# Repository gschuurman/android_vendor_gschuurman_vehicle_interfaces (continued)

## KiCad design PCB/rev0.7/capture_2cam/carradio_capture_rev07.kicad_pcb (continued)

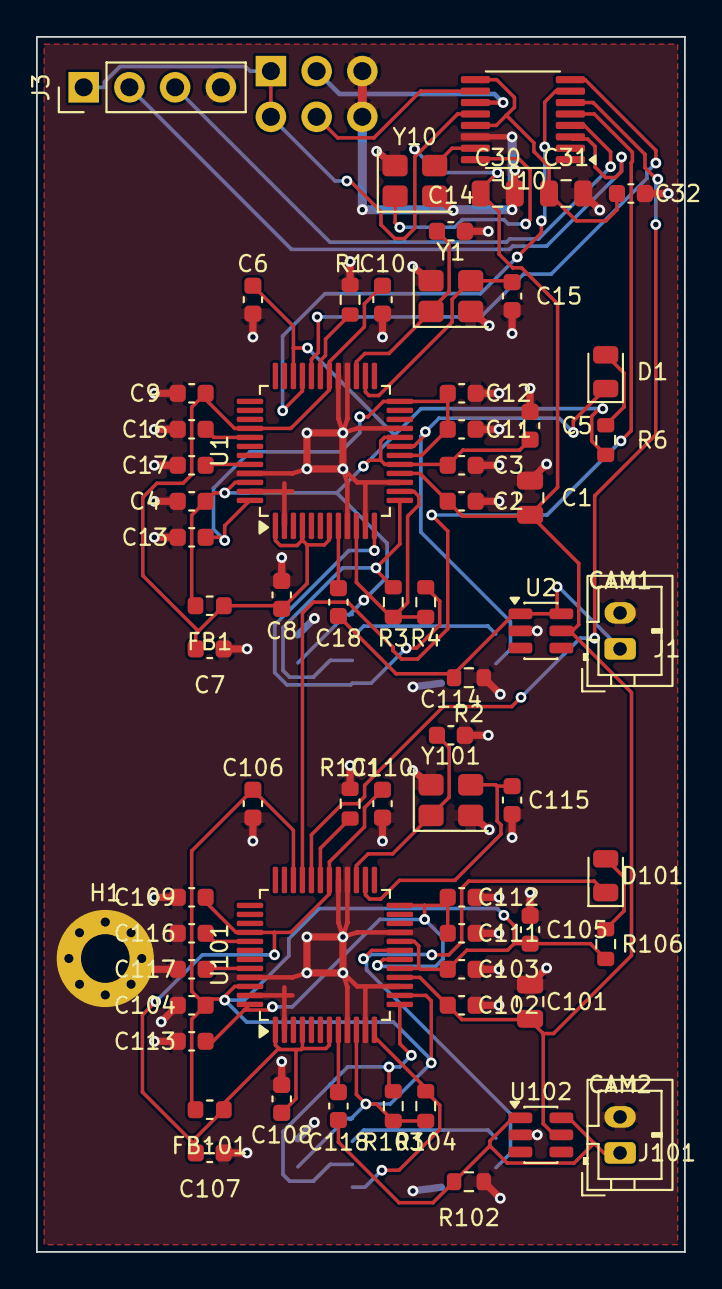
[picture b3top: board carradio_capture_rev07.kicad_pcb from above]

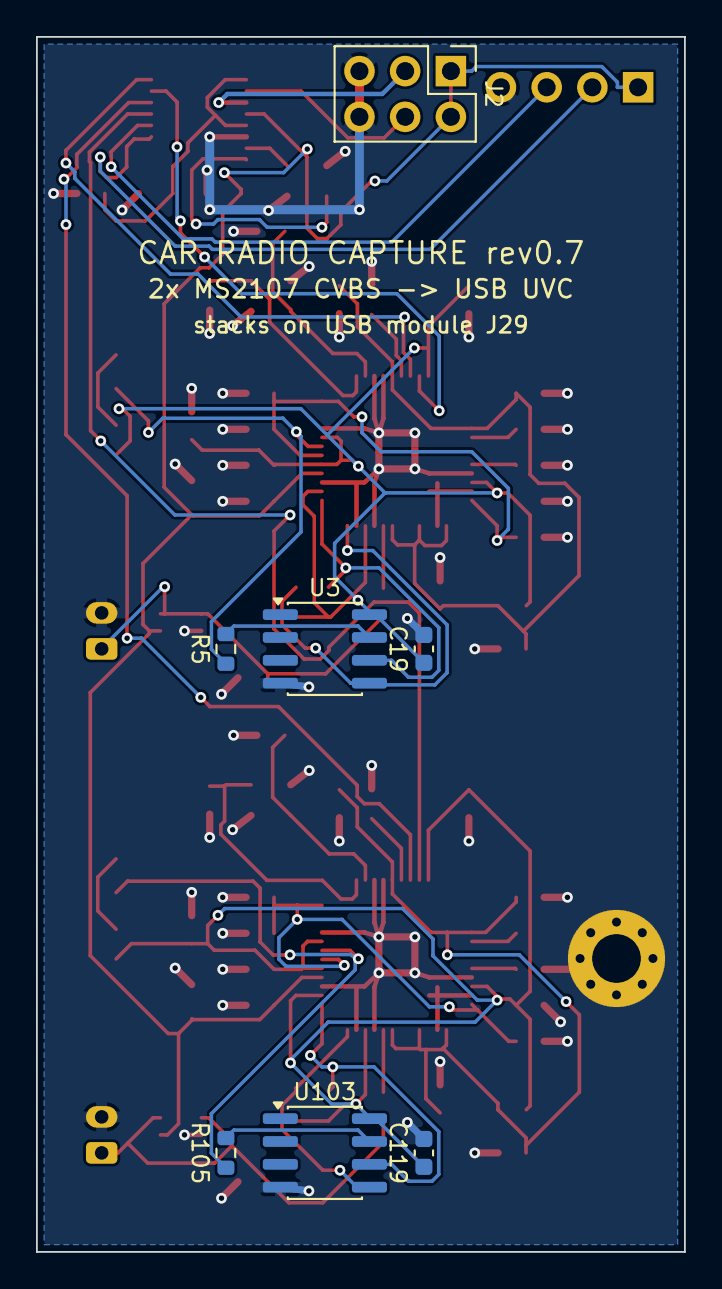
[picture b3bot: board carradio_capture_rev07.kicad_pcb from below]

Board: 2 copper layers, 36.0 x 67.5 mm, 72 parts (7 on the bottom side), 43 nets.

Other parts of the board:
H1: MountingHole_2.7mm_M2.5_Pad_Via

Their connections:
GND: H1.1; also elsewhere on the board

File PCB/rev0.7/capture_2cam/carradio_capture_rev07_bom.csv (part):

Designator,Value,Description / MPN,LCSC,Footprint (KiCad name),Fit,Note
J2,USB module plug,XFCN PZ254V-12-6P 2x3 2.54mm male header (underside),C492420,Connector_PinHeader_2.54mm:PinHeader_2x03_P2.54mm_Vertical,yes,plugs into the 2x3 socket on the USB module: hub 2 port 4 and its own 1 A PTC from +5V_SYS; feeds the on-board hub U10
U1,MS2107,"MacroSilicon MS2107 CVBS/S-Video to USB 2.0 UVC capture, LQFP-48 7x7 0.5mm",C42374499,Package_QFP:LQFP-48_7x7mm_P0.5mm,yes,"UVC 1.0 / UAC 1.0, no driver needed; YUV422 720x576/480 or MJPEG; 0-70 C rated. SVYIN/SVCIN/G1IN, I2S and line-in unused (open). GPIO0 open = internal audio ADC (default)"
C1,10uF,Samsung CL21A106KAYNNNE 0805 10uF 25V X5R,C15850,Capacitor_SMD:C_0805_2012Metric,yes,bulk at the module plug
C2,100nF,YAGEO CC0603KRX7R9BB104 0603 100nF 50V X7R,C14663,Capacitor_SMD:C_0603_1608Metric,yes,at pin 16
C3,4.7uF,Samsung CL10A475KO8NNNC 0603 4.7uF 16V X5R,C19666,Capacitor_SMD:C_0603_1608Metric,yes,VLDO33 output cap at pin 17
C4,100nF,YAGEO CC0603KRX7R9BB104 0603 100nF 50V X7R,C14663,Capacitor_SMD:C_0603_1608Metric,yes,DVDD33 pins 10/14
C5,100nF,YAGEO CC0603KRX7R9BB104 0603 100nF 50V X7R,C14663,Capacitor_SMD:C_0603_1608Metric,yes,DVDD33 pins 20/34
C6,100nF,YAGEO CC0603KRX7R9BB104 0603 100nF 50V X7R,C14663,Capacitor_SMD:C_0603_1608Metric,yes,DVDD33 pin 46
FB1,220Ω@100MHz,Murata BLM18PG221SN1D 0603 ferrite 1.4A,C80165,Inductor_SMD:L_0603_1608Metric,yes,"separates the analog 3.3 V (video/audio ADC, USB PHY) from the digital 3.3 V"
C7,4.7uF,Samsung CL10A475KO8NNNC 0603 4.7uF 16V X5R,C19666,Capacitor_SMD:C_0603_1608Metric,yes,
C8,100nF,YAGEO CC0603KRX7R9BB104 0603 100nF 50V X7R,C14663,Capacitor_SMD:C_0603_1608Metric,yes,AVDD33 pins 1/4
C9,100nF,YAGEO CC0603KRX7R9BB104 0603 100nF 50V X7R,C14663,Capacitor_SMD:C_0603_1608Metric,yes,AVDD33 pin 7 / AVDD33_AU pin 40
C10,100nF,YAGEO CC0603KRX7R9BB104 0603 100nF 50V X7R,C14663,Capacitor_SMD:C_0603_1608Metric,yes,AVDD33_USB pin 30
C11,4.7uF,Samsung CL10A475KO8NNNC 0603 4.7uF 16V X5R,C19666,Capacitor_SMD:C_0603_1608Metric,yes,VLDO12 output cap at pin 18
C12,100nF,YAGEO CC0603KRX7R9BB104 0603 100nF 50V X7R,C14663,Capacitor_SMD:C_0603_1608Metric,yes,DVDD12 pin 24
C13,100nF,YAGEO CC0603KRX7R9BB104 0603 100nF 50V X7R,C14663,Capacitor_SMD:C_0603_1608Metric,yes,AVDD12 pin 48
Y1,12MHz,YXC X322512MSB4SI 12MHz 3225,C9002,Crystal:Crystal_SMD_3225-4Pin_3.2x2.5mm,yes,same crystal as the hubs
C14,22pF,0603 22pF 50V C0G,C1653,Capacitor_SMD:C_0603_1608Metric,yes,load cap (eval board: 10 pF with its crystal; 22 pF suits the 20 pF-load X322512MSB4SI)
C15,22pF,0603 22pF 50V C0G,C1653,Capacitor_SMD:C_0603_1608Metric,yes,
R1,4.7kΩ,UNI-ROYAL 0603WAF4701T5E 4.7k 1%,C23162,Resistor_SMD:R_0603_1608Metric,yes,REXT 4.7k 1% to GND (datasheet)
C16,1uF,Murata GRM188R61H105KAALD 0603 1uF 50V X5R,C77386,Capacitor_SMD:C_0603_1608Metric,yes,audio ADC reference decoupling (eval board); line-in itself unused
C17,1uF,Murata GRM188R61H105KAALD 0603 1uF 50V X5R,C77386,Capacitor_SMD:C_0603_1608Metric,yes,
J1,Camera video in,JST B2B-PH-K-S,C131337,Connector_JST:JST_PH_B2B-PH-K_1x02_P2.00mm_Vertical,yes,"pin 1 camera video (RCA centre), pin 2 camera video ground (RCA shell); lead to an RCA socket. Camera 12 V comes from the reverse lamp as usual"
R2,75Ω,UNI-ROYAL 0603WAF750JT5E 75R 1%,C4275,Resistor_SMD:R_0603_1608Metric,yes,75 ohm line termination
C18,47nF,Samsung CL10B473KB8NNNC 0603 47nF 50V X7R,C1622,Capacitor_SMD:C_0603_1608Metric,yes,AC coupling into AVIN (pin 8)
U2,USBLC6-2SC6,ST USBLC6-2SC6,C7519,Package_TO_SOT_SMD:SOT-23-6,yes,"ESD on the camera line (car wiring); one channel, pass the trace straight through pins 1-6"
U3,24LC16B,Microchip 24LC16B-I/SN,C1349383,Package_SO:SOIC-8_3.9x4.9mm_P1.27mm,DNP,"optional, not fitted: without it the MS2107 enumerates as 534d:0021 'USB Video' with the default modes. Fit to customise via ms-tools"
C19,100nF,YAGEO CC0603KRX7R9BB104 0603 100nF 50V X7R,C14663,Capacitor_SMD:C_0603_1608Metric,yes,EEPROM decoupling
R3,4.7kΩ,UNI-ROYAL 0603WAF4701T5E 4.7k 1%,C23162,Resistor_SMD:R_0603_1608Metric,yes,I2C pull-ups keep GPIO2/3 defined with or without the EEPROM
R4,4.7kΩ,UNI-ROYAL 0603WAF4701T5E 4.7k 1%,C23162,Resistor_SMD:R_0603_1608Metric,yes,
R5,0Ω,UNI-ROYAL 0603WAF0000T5E 0R,C21189,Resistor_SMD:R_0603_1608Metric,DNP,eval board option: WP from GPIO4; open = WP held low inside the 24LC16B (writable)
R6,1kΩ,UNI-ROYAL 0603WAF1001T5E 1k 1%,C21190,Resistor_SMD:R_0603_1608Metric,yes,
D1,LED green,KT-0805G green LED,C2297,LED_SMD:LED_0805_2012Metric,yes,GPIO4 sinks: on while the capture streams (MS2106 eval board behaviour)
U101,MS2107,"MacroSilicon MS2107 CVBS/S-Video to USB 2.0 UVC capture, LQFP-48 7x7 0.5mm",C42374499,Package_QFP:LQFP-48_7x7mm_P0.5mm,yes,"UVC 1.0 / UAC 1.0, no driver needed; YUV422 720x576/480 or MJPEG; 0-70 C rated. SVYIN/SVCIN/G1IN, I2S and line-in unused (open). GPIO0 open = internal audio ADC (default)"
C101,10uF,Samsung CL21A106KAYNNNE 0805 10uF 25V X5R,C15850,Capacitor_SMD:C_0805_2012Metric,yes,bulk at the module plug
C102,100nF,YAGEO CC0603KRX7R9BB104 0603 100nF 50V X7R,C14663,Capacitor_SMD:C_0603_1608Metric,yes,at pin 16
C103,4.7uF,Samsung CL10A475KO8NNNC 0603 4.7uF 16V X5R,C19666,Capacitor_SMD:C_0603_1608Metric,yes,VLDO33 output cap at pin 17
C104,100nF,YAGEO CC0603KRX7R9BB104 0603 100nF 50V X7R,C14663,Capacitor_SMD:C_0603_1608Metric,yes,DVDD33 pins 10/14
C105,100nF,YAGEO CC0603KRX7R9BB104 0603 100nF 50V X7R,C14663,Capacitor_SMD:C_0603_1608Metric,yes,DVDD33 pins 20/34
C106,100nF,YAGEO CC0603KRX7R9BB104 0603 100nF 50V X7R,C14663,Capacitor_SMD:C_0603_1608Metric,yes,DVDD33 pin 46
FB101,220Ω@100MHz,Murata BLM18PG221SN1D 0603 ferrite 1.4A,C80165,Inductor_SMD:L_0603_1608Metric,yes,"separates the analog 3.3 V (video/audio ADC, USB PHY) from the digital 3.3 V"
C107,4.7uF,Samsung CL10A475KO8NNNC 0603 4.7uF 16V X5R,C19666,Capacitor_SMD:C_0603_1608Metric,yes,
C108,100nF,YAGEO CC0603KRX7R9BB104 0603 100nF 50V X7R,C14663,Capacitor_SMD:C_0603_1608Metric,yes,AVDD33 pins 1/4
C109,100nF,YAGEO CC0603KRX7R9BB104 0603 100nF 50V X7R,C14663,Capacitor_SMD:C_0603_1608Metric,yes,AVDD33 pin 7 / AVDD33_AU pin 40
C110,100nF,YAGEO CC0603KRX7R9BB104 0603 100nF 50V X7R,C14663,Capacitor_SMD:C_0603_1608Metric,yes,AVDD33_USB pin 30
C111,4.7uF,Samsung CL10A475KO8NNNC 0603 4.7uF 16V X5R,C19666,Capacitor_SMD:C_0603_1608Metric,yes,VLDO12 output cap at pin 18
C112,100nF,YAGEO CC0603KRX7R9BB104 0603 100nF 50V X7R,C14663,Capacitor_SMD:C_0603_1608Metric,yes,DVDD12 pin 24
C113,100nF,YAGEO CC0603KRX7R9BB104 0603 100nF 50V X7R,C14663,Capacitor_SMD:C_0603_1608Metric,yes,AVDD12 pin 48
Y101,12MHz,YXC X322512MSB4SI 12MHz 3225,C9002,Crystal:Crystal_SMD_3225-4Pin_3.2x2.5mm,yes,same crystal as the hubs
C114,22pF,0603 22pF 50V C0G,C1653,Capacitor_SMD:C_0603_1608Metric,yes,load cap (eval board: 10 pF with its crystal; 22 pF suits the 20 pF-load X322512MSB4SI)
C115,22pF,0603 22pF 50V C0G,C1653,Capacitor_SMD:C_0603_1608Metric,yes,
R101,4.7kΩ,UNI-ROYAL 0603WAF4701T5E 4.7k 1%,C23162,Resistor_SMD:R_0603_1608Metric,yes,REXT 4.7k 1% to GND (datasheet)
C116,1uF,Murata GRM188R61H105KAALD 0603 1uF 50V X5R,C77386,Capacitor_SMD:C_0603_1608Metric,yes,audio ADC reference decoupling (eval board); line-in itself unused
C117,1uF,Murata GRM188R61H105KAALD 0603 1uF 50V X5R,C77386,Capacitor_SMD:C_0603_1608Metric,yes,
J101,Camera video in,JST B2B-PH-K-S,C131337,Connector_JST:JST_PH_B2B-PH-K_1x02_P2.00mm_Vertical,yes,"pin 1 camera video (RCA centre), pin 2 camera video ground (RCA shell); lead to an RCA socket. Camera 12 V comes from the reverse lamp as usual"
R102,75Ω,UNI-ROYAL 0603WAF750JT5E 75R 1%,C4275,Resistor_SMD:R_0603_1608Metric,yes,75 ohm line termination
C118,47nF,Samsung CL10B473KB8NNNC 0603 47nF 50V X7R,C1622,Capacitor_SMD:C_0603_1608Metric,yes,AC coupling into AVIN (pin 8)
U102,USBLC6-2SC6,ST USBLC6-2SC6,C7519,Package_TO_SOT_SMD:SOT-23-6,yes,"ESD on the camera line (car wiring); one channel, pass the trace straight through pins 1-6"
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
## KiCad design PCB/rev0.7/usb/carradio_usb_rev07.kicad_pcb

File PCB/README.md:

# Peripheral board (mainboard)

This is the board that connects the VIM3 and the Raspberry Pi Pico 2 (vehicle MCU, firmware in `../mcu`)
to the car through the ISO 10487 harness. It also carries the audio DACs, GNSS, the display adapter, the
USB hub and the 5V supply.

- `rev0.7/` is the newest set of modules: the audio module with the car mic input (`audio/`, 2x PCM5102A + PCM1808),
  the USB module and the camera capture module (`capture_1cam/`, `capture_2cam/`). The main and GNSS boards stay at rev 0.6.
  Each folder has a README with the ordering and soldering notes.
- `rev0.6/` is the built and bench-tested main board, USB module and GNSS module, plus `stencil_jig/`.
- `rev0.5/` and `rev0.4/` are the earlier split versions (main board plus plug-in modules).
- `rev0.3/` is the single board with the RP2350B chip on it instead of the Pico 2 module.
  Read `DESIGN_rev03.md` for the changes, the 48-GPIO map and the RP2350-E9 check.
- `rev0.2/` is the Pico 2 version, and its documents still describe everything rev 0.3 didn't change.
  Start with `PCB_SUMMARY_rev02.md`, then read:
  - `DESIGN_rev02.md` for the pin map and design notes
  - `DESIGN_REVIEW_rev02.md` for the design check and layout rules
  - `ORDERING_rev02.md` for LCSC parts, cost and what to check before ordering
- `rev0.1/` is the first draft, kept for reference.
- `AUDIO.md` is the audio output plan.

The schematics are generated KiCad 7 files, for import into EasyEDA Pro. To regenerate one, run
`python3 gen3.py` inside `rev0.3/` (or `gen2.py` inside `rev0.2/`).

Rev 0.3 and later are laid out in KiCad (open with KiCad 10).

## Bring-up wizards

Each board of rev 0.6 and rev 0.7 has a step-by-step bench wizard (`WIZARD.html`) next to its design. See `wizard/README.md`.

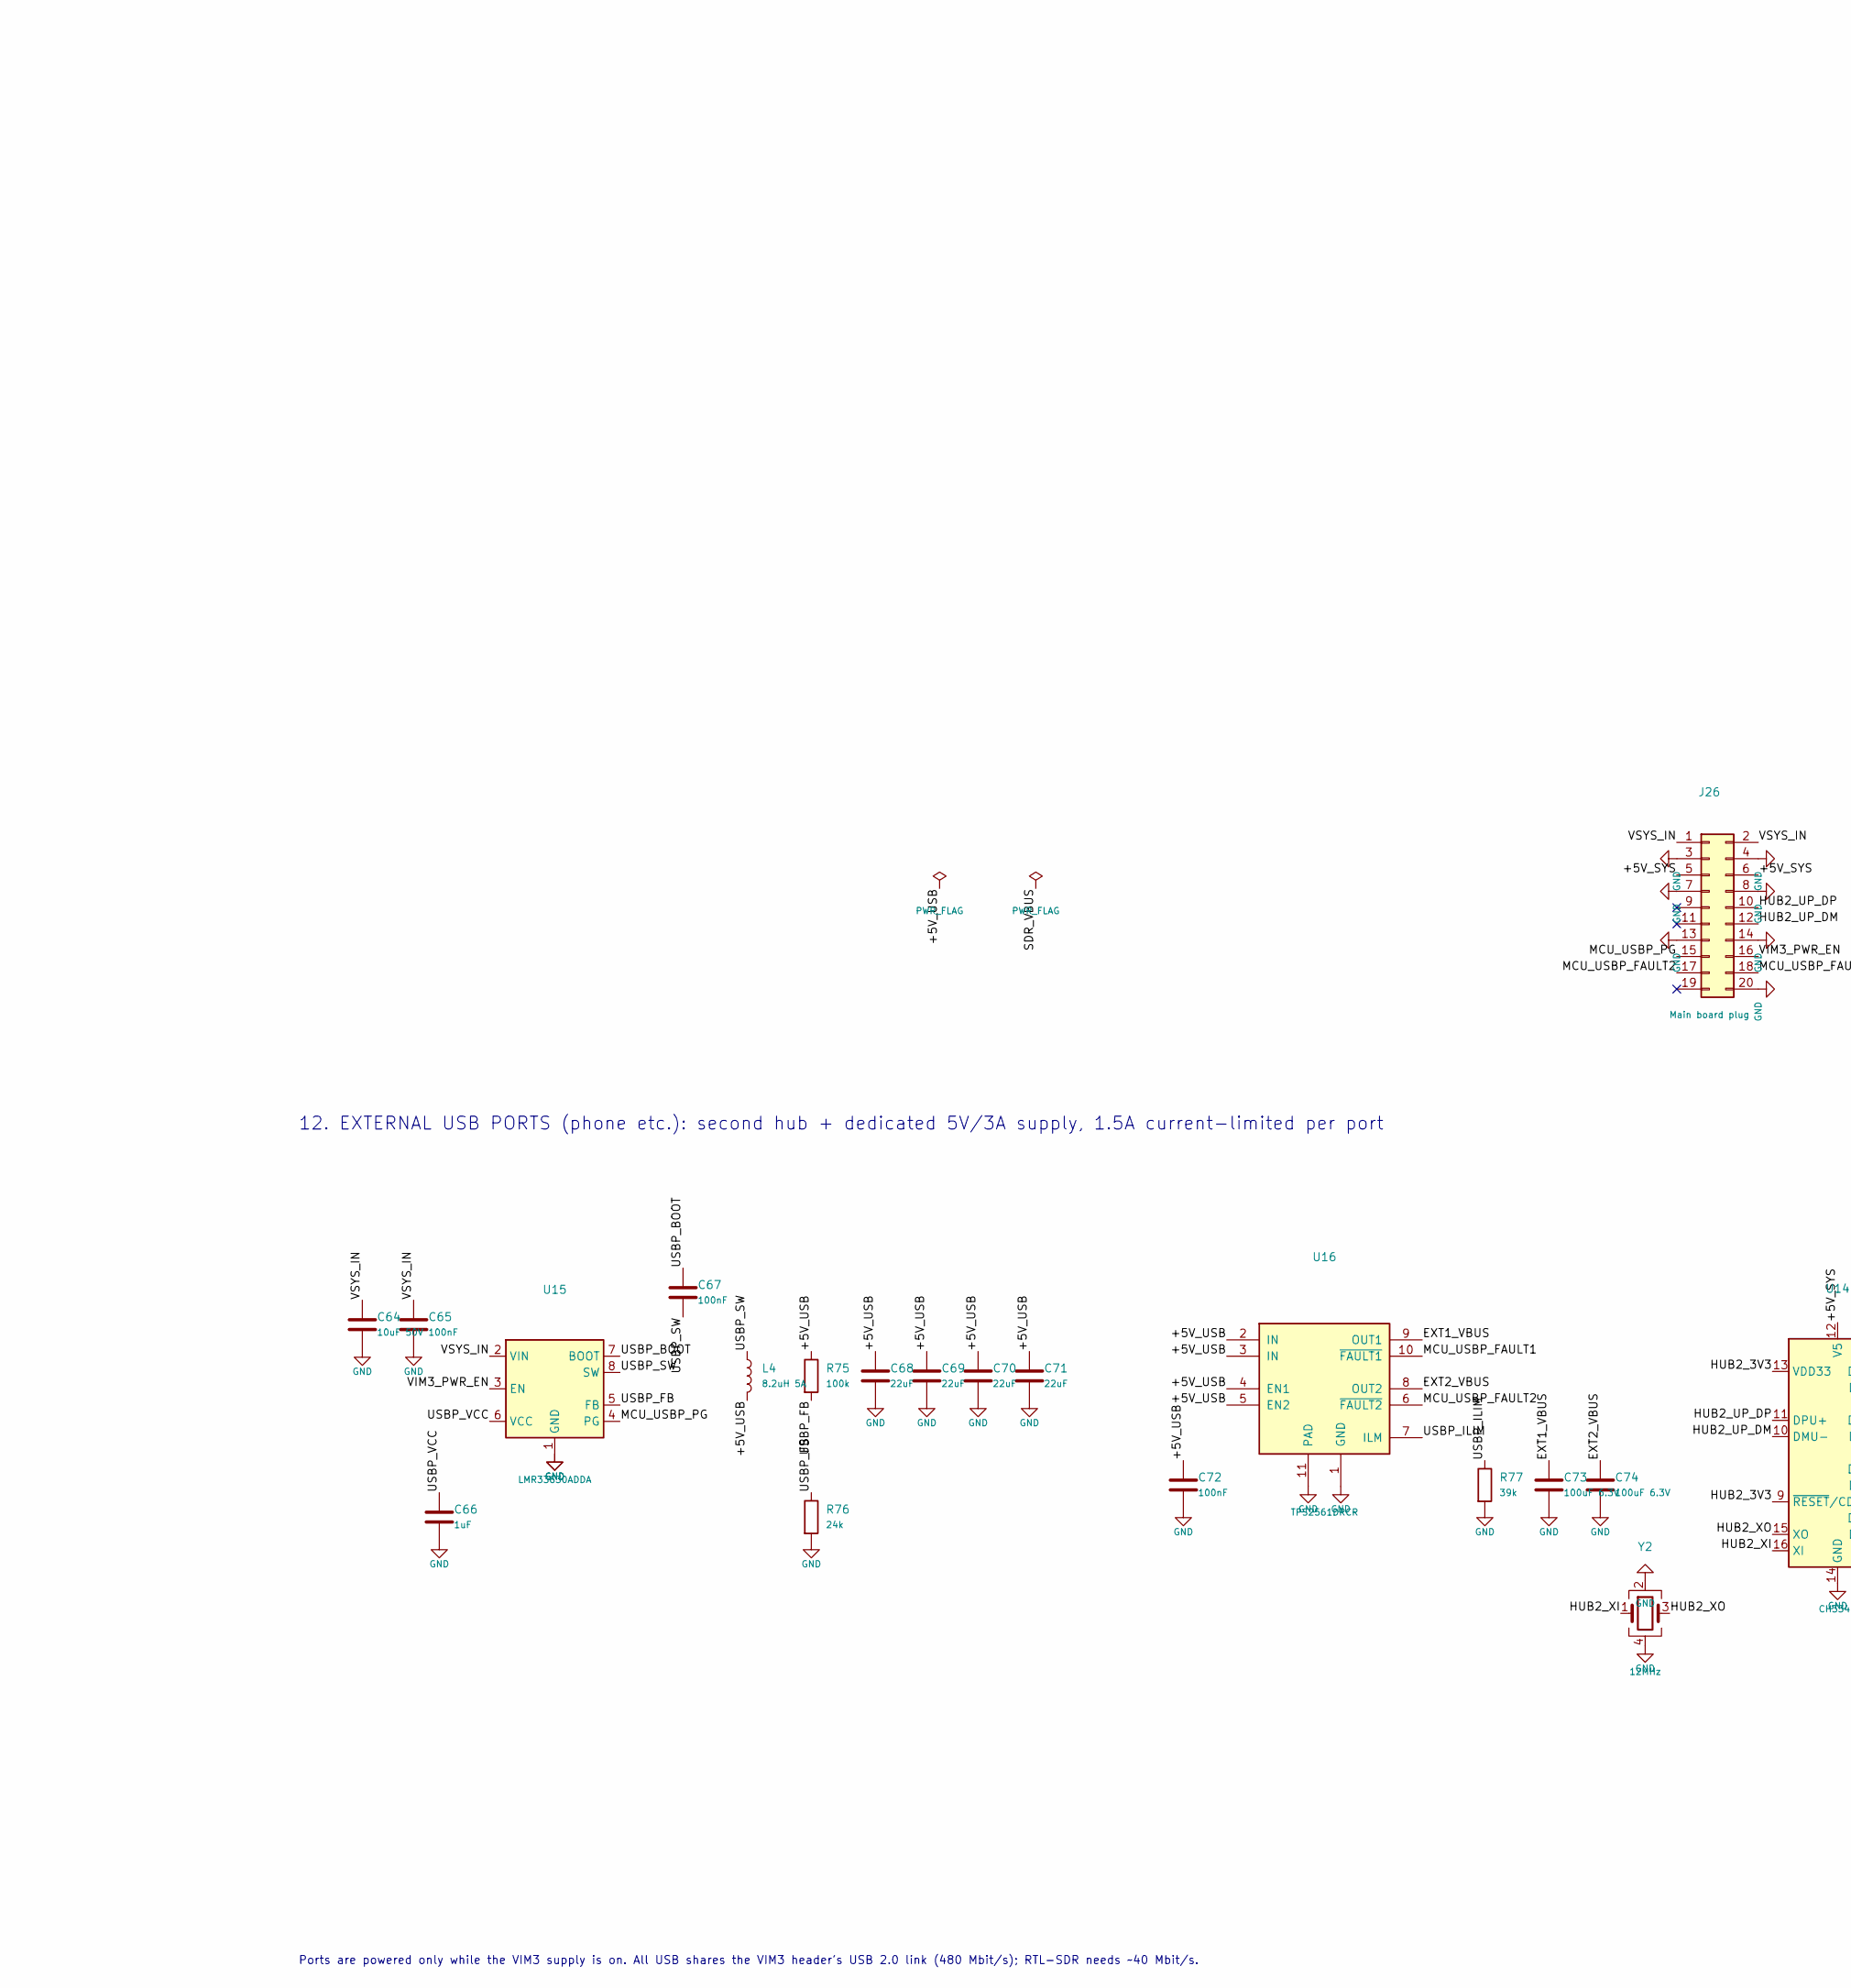
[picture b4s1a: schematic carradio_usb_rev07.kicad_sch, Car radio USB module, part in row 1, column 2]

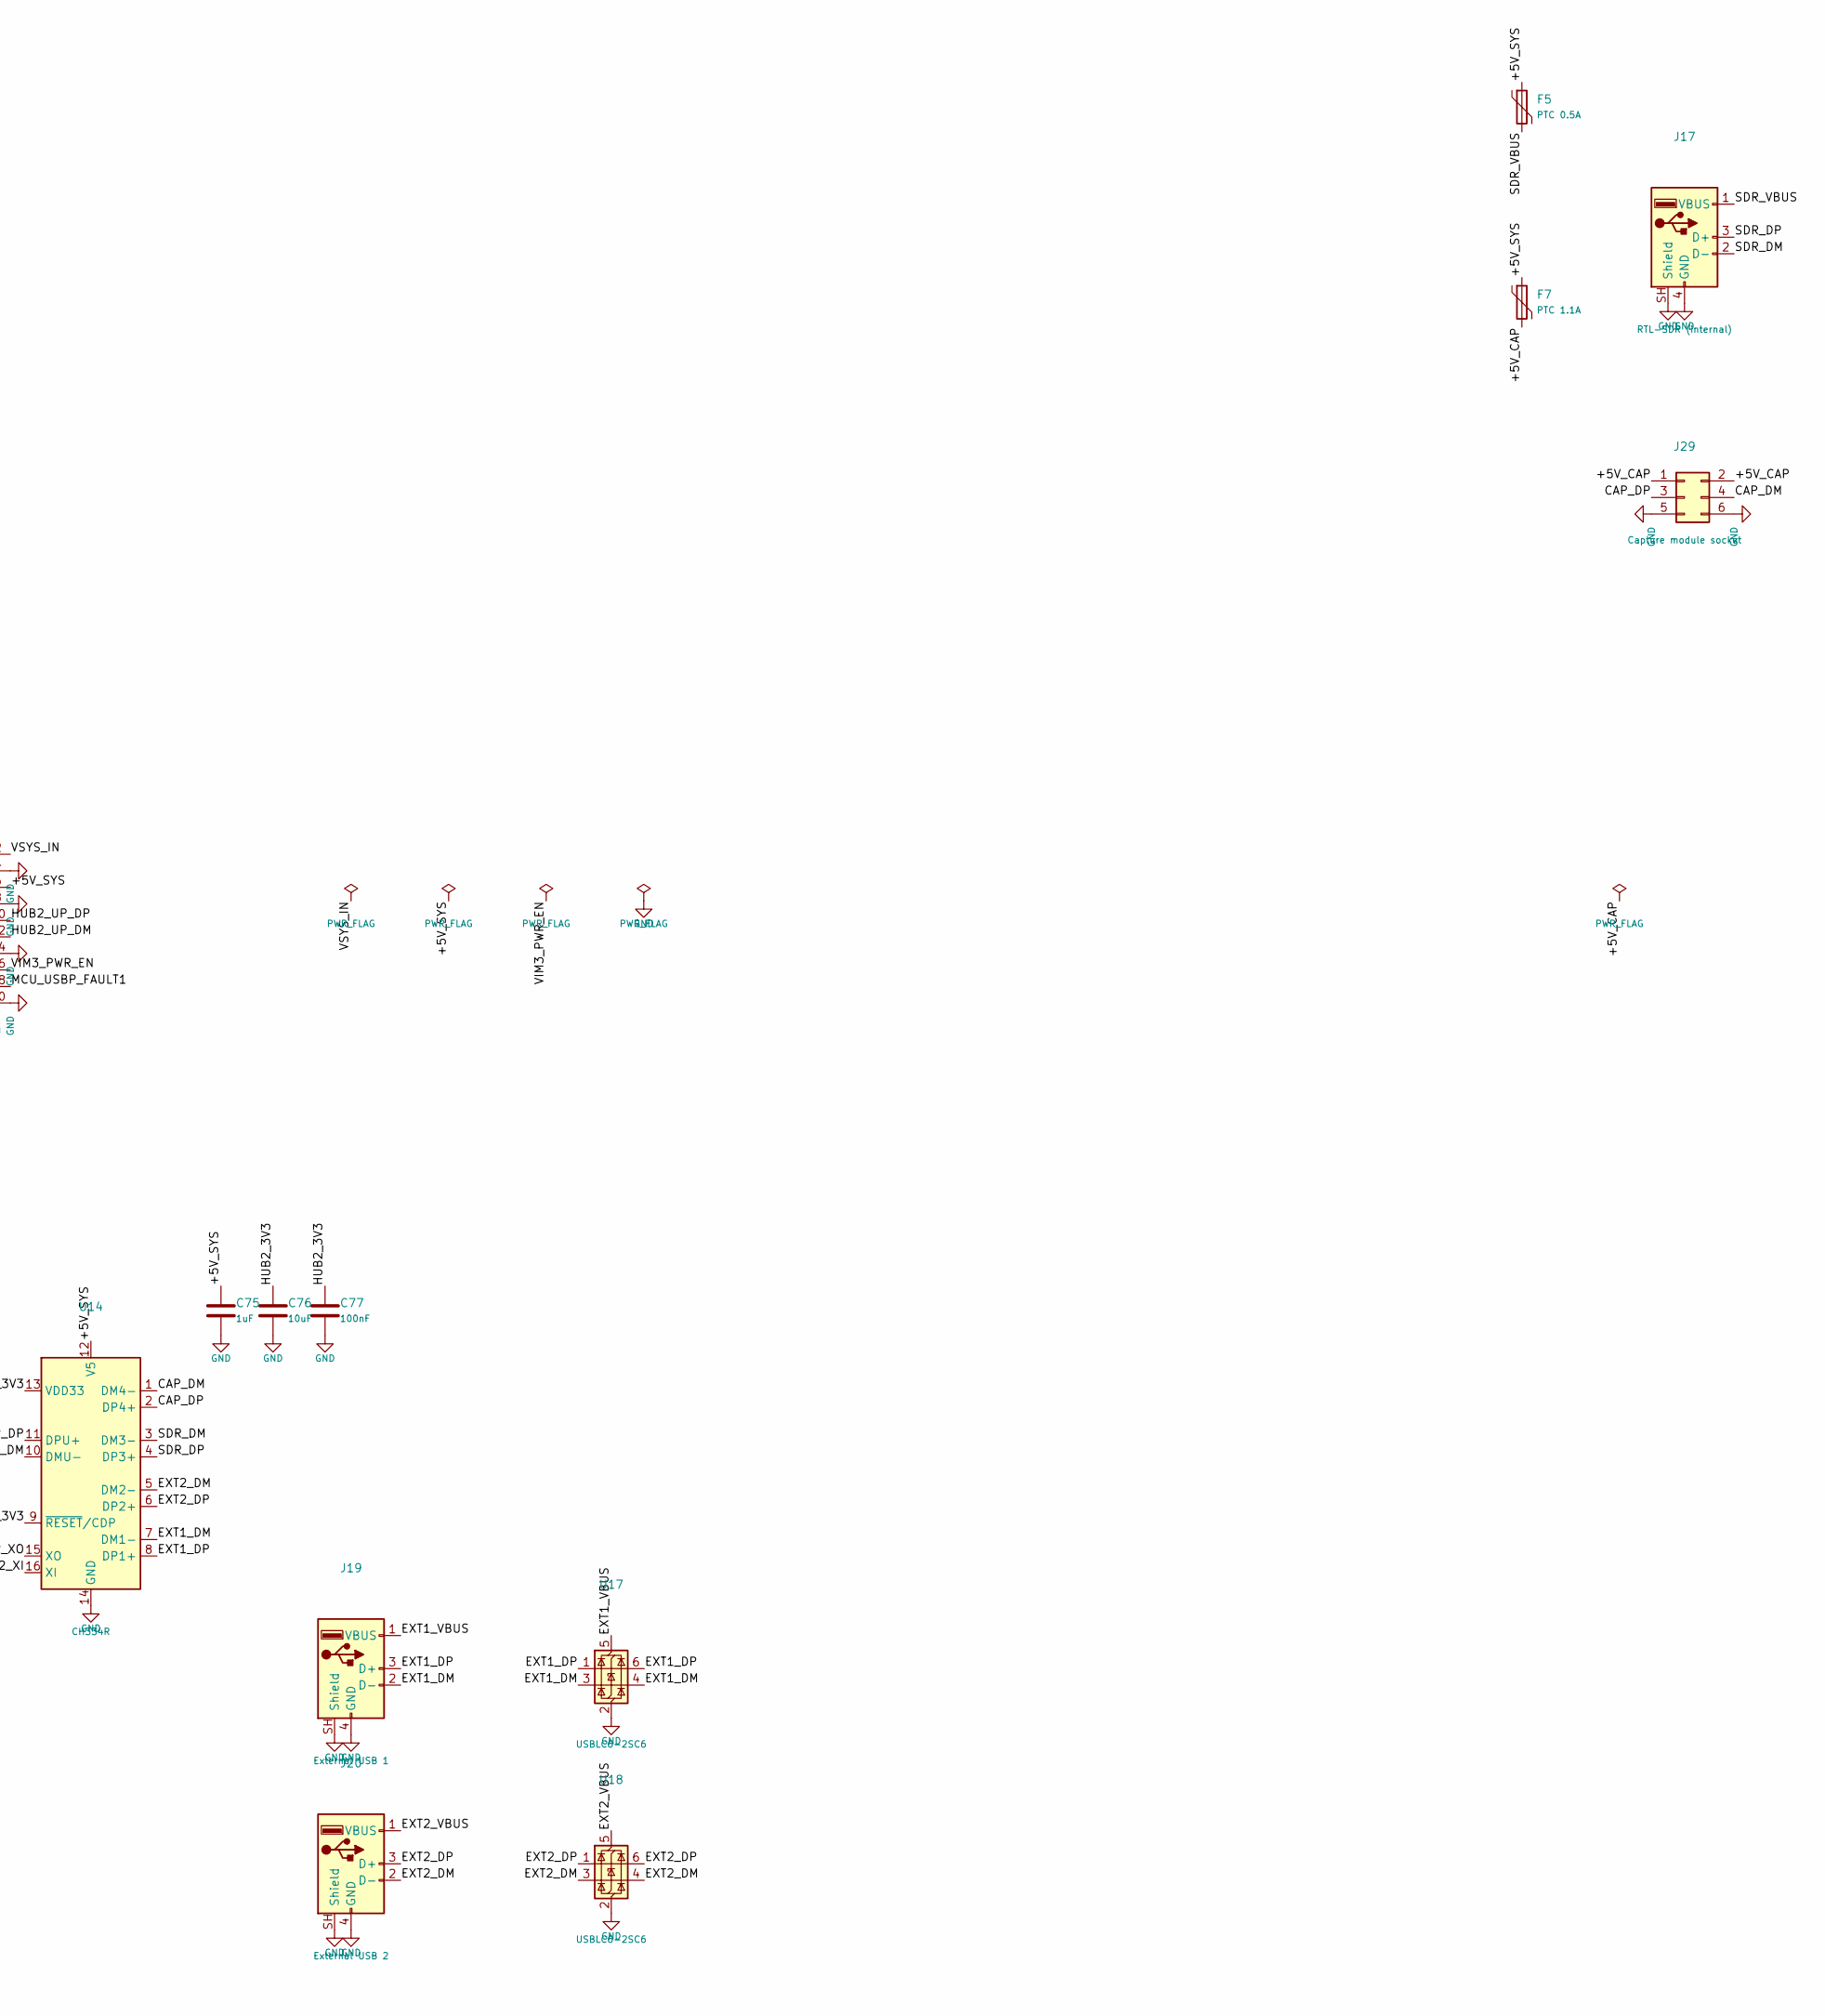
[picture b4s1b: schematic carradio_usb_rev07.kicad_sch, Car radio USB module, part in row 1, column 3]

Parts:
C64: 10uF 50V; C_1206_3216Metric; MPN 1206 10uF 50V X5R (Murata GRM31CR61H106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; LCSC C77092
C65, C67, C72, C77: 100nF; C_0603_1608Metric; MPN 0603 100nF 50V X7R; LCSC C14663
C66, C75: 1uF; C_0603_1608Metric; MPN 0603 1uF 50V X5R (Murata GRM188R61H105K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; LCSC C77386
C68, C69, C70, C71: 22uF; C_0805_2012Metric; MPN 0805 22uF 25V X5R; LCSC C45783
C73, C74: 100uF 6.3V; C_1206_3216Metric; MPN 1206 100uF 6.3V X5R; LCSC C15008
C76: 10uF; C_0805_2012Metric; MPN 0805 10uF 25V X5R; LCSC C15850
F5: PTC 0.5A; Fuse_1206_3216Metric; MPN Bourns MF-NSMF050-2; LCSC C75464
F7: PTC 1.1A; Fuse_1206_3216Metric; MPN Bourns MF-NSMF110-2; LCSC C89654
J17: RTL-SDR (internal); USB_A_Molex_67643_Horizontal; MPN Molex 67643-0910 USB-A; LCSC C2798029
J19: External USB 1; USB_A_Molex_67643_Horizontal; MPN Molex 67643-0910 USB-A; LCSC C2798029
J20: External USB 2; USB_A_Molex_67643_Horizontal; MPN Molex 67643-0910 USB-A; LCSC C2798029
J26: Main board plug; PinHeader_2x10_P2.54mm_Vertical; MPN ZHOURI 2.54-2*10 male pin header; LCSC C5116480
J29: Capture module socket; PinSocket_2x03_P2.54mm_Vertical; MPN CJT A2541HWV-2x3P 2x3 2.54mm female soc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; LCSC C239343
L4: 8.2uH 5A; L_Coilcraft_XAL6060-XXX; MPN Coilcraft XAL6060-822MEC 8.2uH Isat 8.4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; LCSC C19191627
R75: 100k; R_0603_1608Metric; MPN 0603 100k 1%; LCSC C25803
R76: 24k; R_0603_1608Metric; MPN 0603 24k 1%; LCSC C23352
R77: 39k; R_0603_1608Metric; MPN 0603 39k 1%; LCSC C23153
U14: CH334R; QSOP-16_3.9x4.9mm_P0.635mm; MPN WCH CH334R 4-port USB 2.0 hub, QSOP-16; LCSC C4154405
U15: LMR33630ADDA; TI_SO-PowerPAD-8_ThermalVias; MPN TI LMR33630ADDAR 36V 3A buck, 400 kHz; LCSC C841384
U16: TPS2561DRCR; VSON-10-1EP_3x3mm_P0.5mm_EP1.65x2.4mm; MPN TI TPS2561DRCR dual 2.8A USB power swit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; LCSC C140303
U17, U18: USBLC6-2SC6; SOT-23-6; MPN ST USBLC6-2SC6; LCSC C7519
Y2: 12MHz; Crystal_SMD_3225-4Pin_3.2x2.5mm; MPN YXC X322512MSB4SI 12MHz; LCSC C9002

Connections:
/+5V_CAP: F7.2, J29.1, J29.2
/+5V_SYS: C75.1, F5.1, F7.1, J26.5, J26.6, U14.12 (V5)
/+5V_USB: C68.1, C69.1, C70.1, C71.1, C72.1, L4.2, R75.1, U16.2 (IN), U16.3 (IN), U16.4 (EN1), U16.5 (EN2)
/CAP_DM: J29.4, U14.1 (DM4-)
/CAP_DP: J29.3, U14.2 (DP4+)
/EXT1_DM: J19.2 (D-), U14.7 (DM1-), U17.3 (I/O2), U17.4 (I/O2)
/EXT1_DP: J19.3 (D+), U14.8 (DP1+), U17.1 (I/O1), U17.6 (I/O1)
/EXT1_VBUS: C73.1, J19.1 (VBUS), U16.9 (OUT1), U17.5 (VBUS)
/EXT2_DM: J20.2 (D-), U14.5 (DM2-), U18.3 (I/O2), U18.4 (I/O2)
/EXT2_DP: J20.3 (D+), U14.6 (DP2+), U18.1 (I/O1), U18.6 (I/O1)
/EXT2_VBUS: C74.1, J20.1 (VBUS), U16.8 (OUT2), U18.5 (VBUS)
/HUB2_3V3: C76.1, C77.1, U14.9 (~RESET/CDP), U14.13 (VDD33)
/HUB2_UP_DM: J26.12, U14.10 (DMU-)
/HUB2_UP_DP: J26.10, U14.11 (DPU+)
/HUB2_XI: U14.16 (XI), Y2.1
/HUB2_XO: U14.15 (XO), Y2.3
/MCU_USBP_FAULT1: J26.18, U16.10 (~FAULT1)
/MCU_USBP_FAULT2: J26.17, U16.6 (~FAULT2)
/MCU_USBP_PG: J26.15, U15.4 (PG)
/SDR_DM: J17.2 (D-), U14.3 (DM3-)
/SDR_DP: J17.3 (D+), U14.4 (DP3+)
/SDR_VBUS: F5.2, J17.1 (VBUS)
/USBP_BOOT: C67.1, U15.7 (BOOT)
/USBP_FB: R75.2, R76.1, U15.5 (FB)
/USBP_ILIM: R77.1, U16.7 (ILM)
/USBP_SW: C67.2, L4.1, U15.8 (SW)
/USBP_VCC: C66.1, U15.6 (VCC)
/VIM3_PWR_EN: J26.16, U15.3 (EN)
/VSYS_IN: C64.1, C65.1, J26.1, J26.2, U15.2 (VIN)
GND: C64.2, C65.2, C66.2, C68.2, C69.2, C70.2, C71.2, C72.2, C73.2, C74.2, C75.2, C76.2, C77.2, J17.4 (GND), J17.SH (Shield), J19.4 (GND), J19.SH (Shield), J20.4 (GND), J20.SH (Shield), J26.3, J26.4, J26.7, J26.8, J26.13, J26.14, J26.20, J29.5, J29.6, R76.2, R77.2, U14.14 (GND), U15.1 (GND), U15.9 (GND), U16.1 (GND), U16.11 (PAD), U17.2 (GND), U18.2 (GND), Y2.2, Y2.4; also elsewhere on the board

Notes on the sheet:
12. EXTERNAL USB PORTS (phone etc.): second hub + dedicated 5V/3A supply, 1.5A current-limited per port
Ports are powered only while the VIM3 supply is on. All USB shares the VIM3 header's USB 2.0 link (480 Mbit/s); RTL-SDR needs ~40 Mbit/s.
Car radio USB module rev 0.7 - phone ports, hub 2, their 5V/3A supply, the RTL-SDR socket and the capture module socket (J29); plugs onto the peripheral board (J26 -> J25). Generated by gen4.py usb.

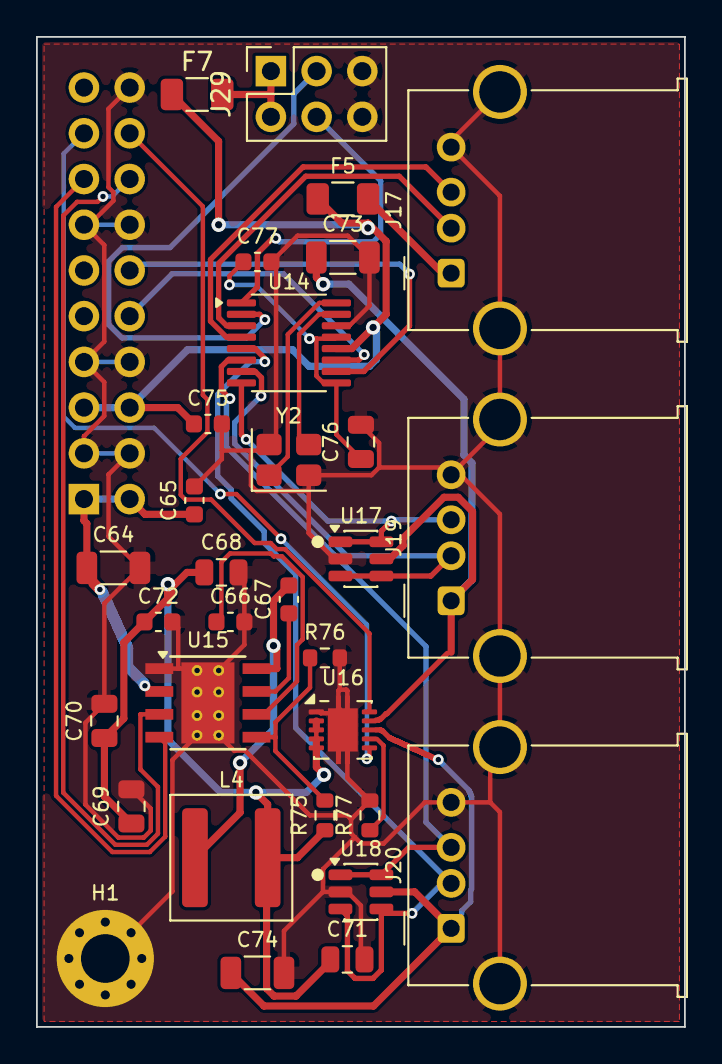
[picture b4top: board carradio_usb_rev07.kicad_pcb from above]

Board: 2 copper layers, 36.0 x 55.0 mm, 32 parts (1 on the bottom side), 30 nets.

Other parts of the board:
H1: M2.5 standoff; MountingHole_2.7mm_M2.5_Pad_Via

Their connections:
GND: H1.1; also elsewhere on the board
